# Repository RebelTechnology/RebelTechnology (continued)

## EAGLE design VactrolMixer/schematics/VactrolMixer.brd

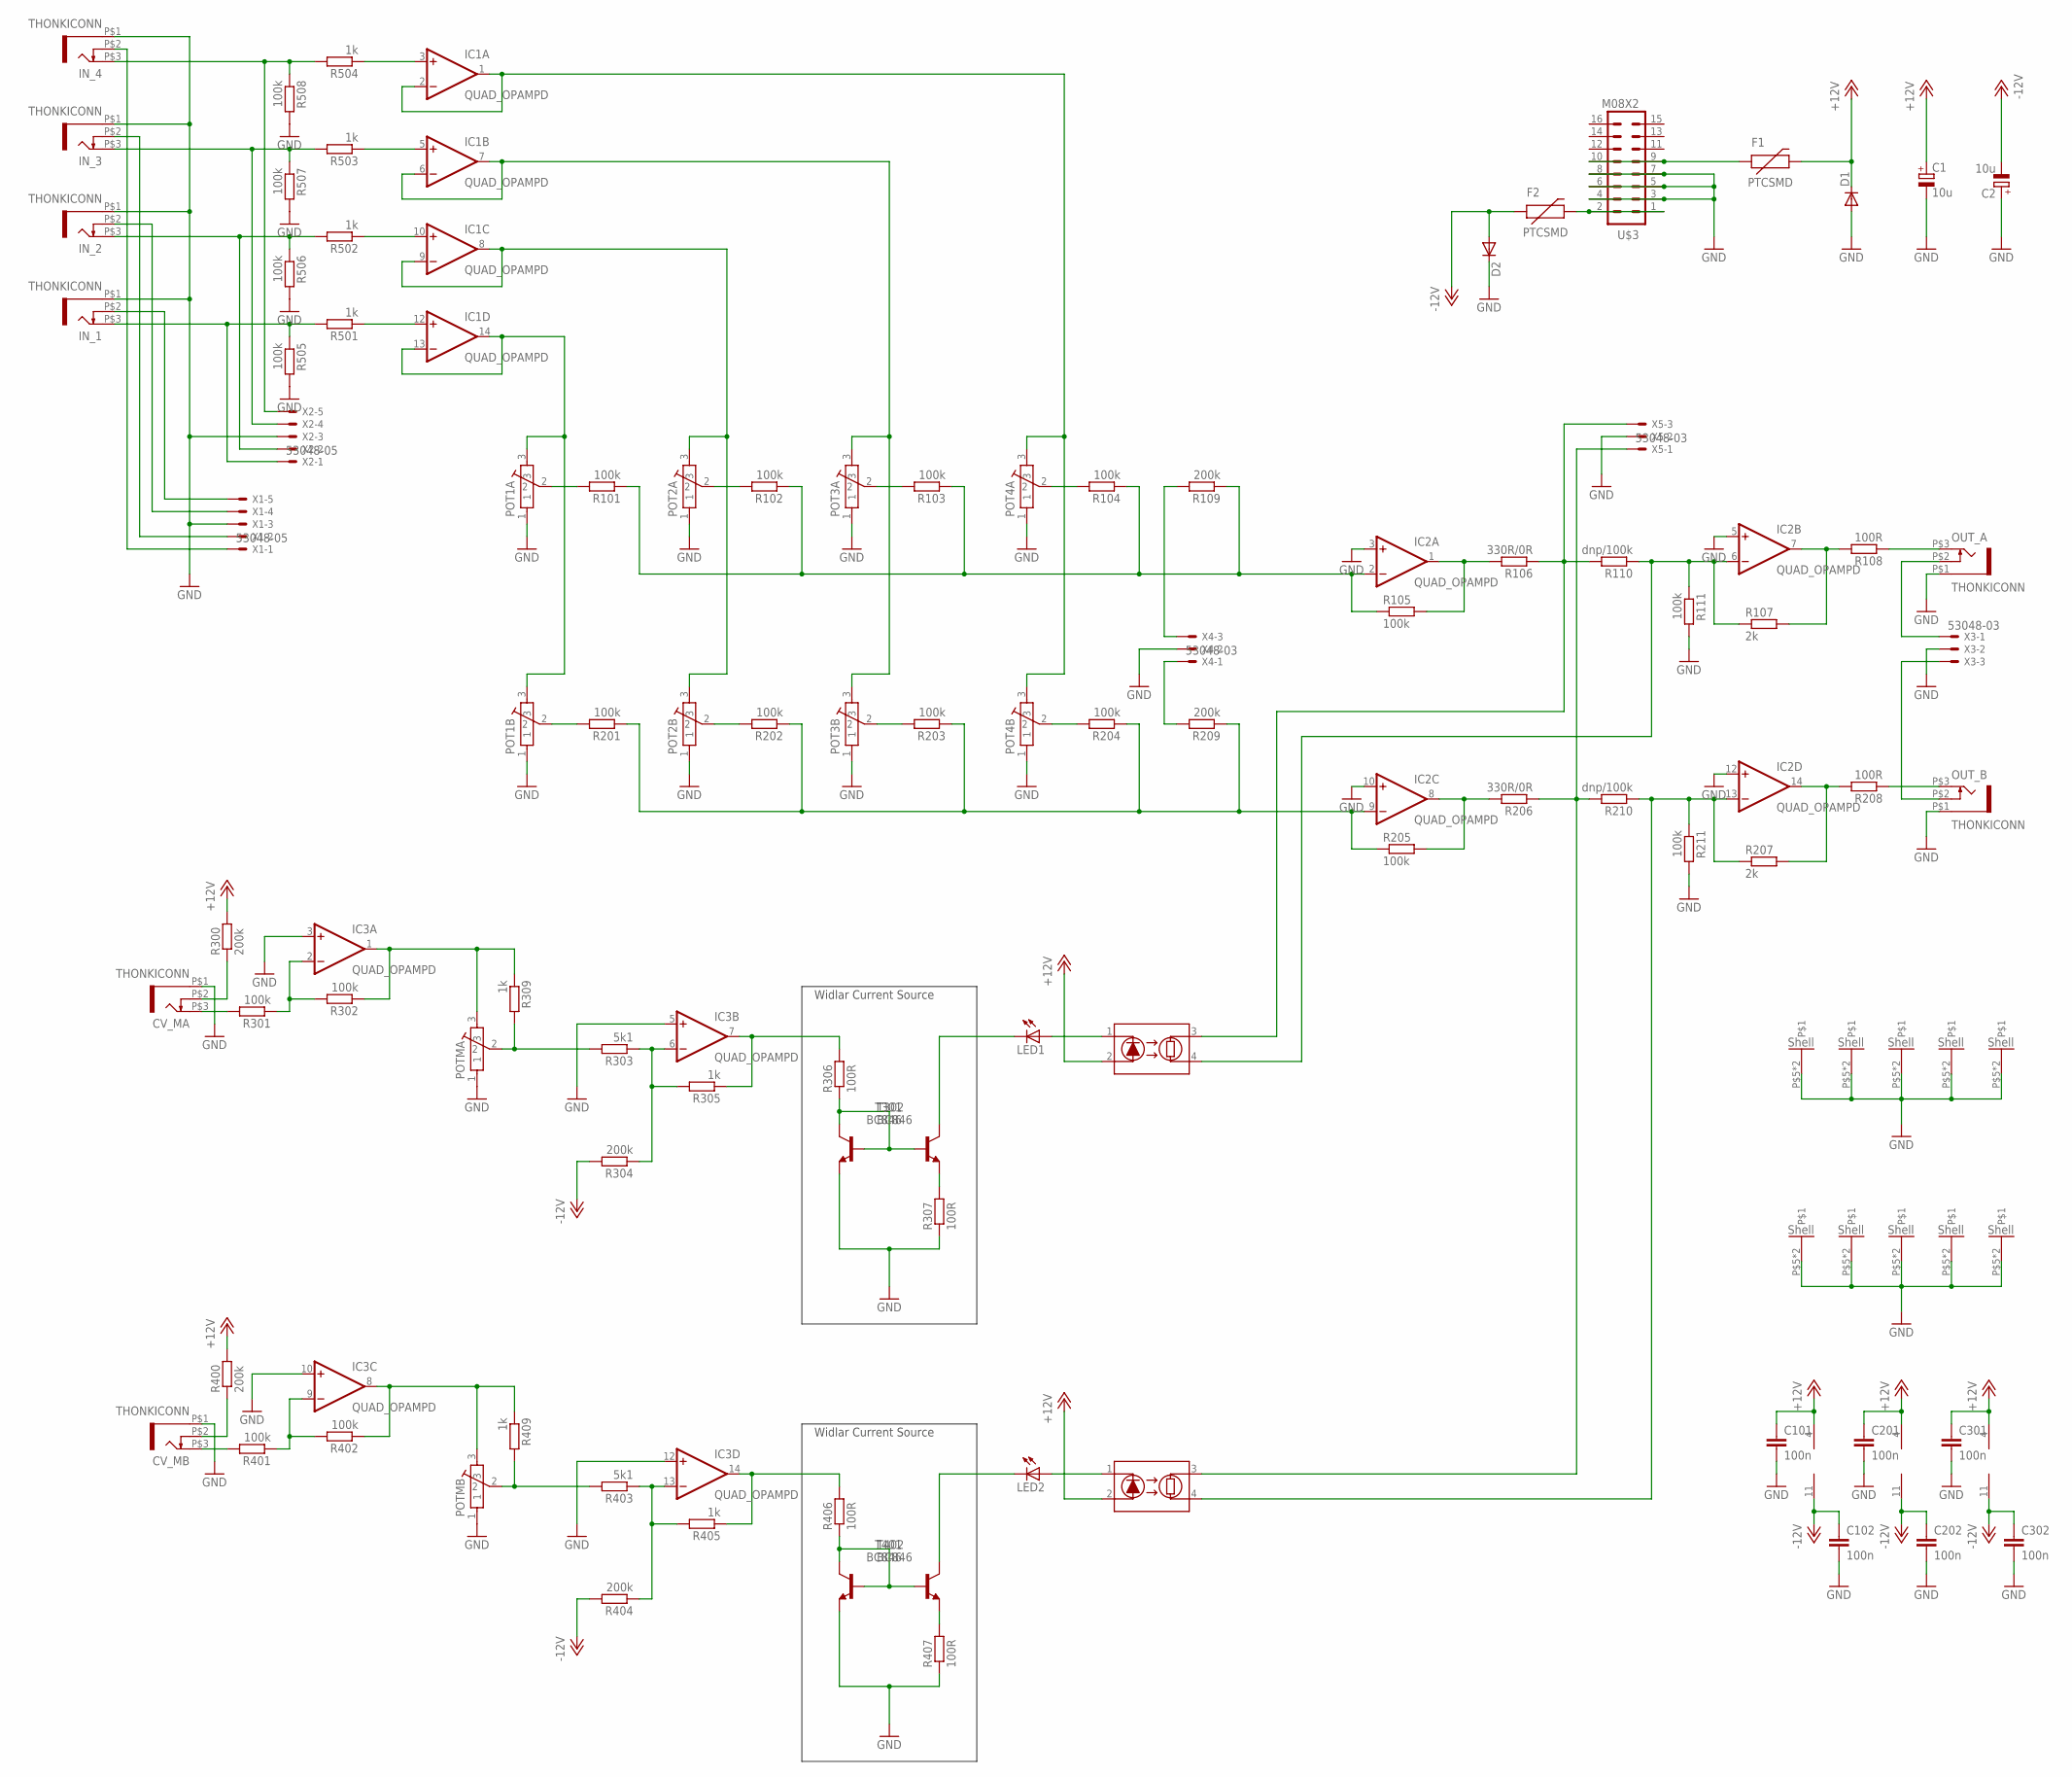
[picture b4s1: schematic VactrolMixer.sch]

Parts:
C1, C2: 10u; 153CLV-0605
C101, C102, C201, C202, C301, C302: 100n; C0603
CV_MA: THONKICONN
CV_MB: THONKICONN
D1, D2: DIODESMA; SMA-DIODE
F1, F2: PTCSMD; PTC-1206
IC1, IC2, IC3: QUAD_OPAMPD; SO14
IN_1, IN_2, IN_3, IN_4: THONKICONN
LED1, LED2: LED3MM
OUT_A: THONKICONN
OUT_B: THONKICONN
POT1A, POT1B, POT2A, POT2B, POT3A, POT3B, POT4A, POT4B: POT-ALPS-RK09L1140
POTMA: POT-ALPS-RK09L1140
POTMB: POT-ALPS-RK09L1140
R101, R102, R103, R104, R105, R111, R201, R202, R203, R204, R205, R211, R301, R302, R401, R402, R505, R506, R507, R508: 100k; R0603
R106, R206: 330R/0R; R0603
R107, R207: 2k; R0603
R108, R208, R306, R307, R406, R407: 100R; R0603
R109, R209, R300, R304, R400, R404: 200k; R0603
R110, R210: dnp/100k; R0603
R303, R403: 5k1; R0603
R305, R309, R405, R409, R501, R502, R503, R504: 1k; R0603
T301, T302, T401, T402: BC846; SOT23
U$3: M08X2; 2X8
VAC1, VAC2: VTL5C3
X1, X2: 53048-05
X3, X4, X5: 53048-03

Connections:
+12V: C1.+, C101.1, C201.1, C301.1, D1.C, F1.2, IC1.4 (V+), IC2.4 (V+), IC3.4 (V+), R300.2, R400.2, VAC1.2 (LED+), VAC2.2 (LED+)
-12V: C2.-, C102.1, C202.1, C302.1, D2.A, F2.1, IC1.11 (V-), IC2.11 (V-), IC3.11 (V-), R304.2, R404.2
CV_SW_A: CV_MA.P$2 (4), R300.1
CV_SW_B: CV_MB.P$2 (4), R400.1
GND: C1.-, C2.+, C101.2, C102.2, C201.2, C202.2, C301.2, C302.2, CV_MA.P$1 (5), CV_MB.P$1 (5), D1.A, D2.C, IC2.3 (+IN), IC2.5 (+IN), IC2.10 (+IN), IC2.12 (+IN), IC3.3 (+IN), IC3.5 (+IN), IC3.10 (+IN), IC3.12 (+IN), IN_1.P$1 (5), IN_2.P$1 (5), IN_3.P$1 (5), IN_4.P$1 (5), OUT_A.P$1 (5), OUT_B.P$1 (5), POT1A.1, POT1A.P$5, POT1A.P$6, POT1B.1, POT1B.P$5, POT1B.P$6, POT2A.1, POT2A.P$5, POT2A.P$6, POT2B.1, POT2B.P$5, POT2B.P$6, POT3A.1, POT3A.P$5, POT3A.P$6, POT3B.1, POT3B.P$5, POT3B.P$6, POT4A.1, POT4A.P$5, POT4A.P$6, POT4B.1, POT4B.P$5, POT4B.P$6, POTMA.1, POTMA.P$5, POTMA.P$6, POTMB.1, POTMB.P$5, POTMB.P$6, R111.2, R211.2, R307.1, R407.1, R505.2, R506.2, R507.2, R508.2, T301.2 (E), T401.2 (E), U$3.3, U$3.4, U$3.5, U$3.6, U$3.7, U$3.8, X1.3, X2.3, X3.2, X4.2, X5.2
INV_OUT_A: R106.1, R110.2, VAC1.3 (LDRA), X5.3
INV_OUT_B: R206.1, R210.2, VAC2.3 (LDRA), X5.1
IN_1: IN_1.P$3 (3), R501.2, R505.1, X2.1
IN_2: IN_2.P$3 (3), R502.2, R506.1, X2.2
IN_3: IN_3.P$3 (3), R503.2, R507.1, X2.4
IN_4: IN_4.P$3 (3), R504.2, R508.1, X2.5
IN_5_A: R109.2, X4.3
IN_5_B: R209.2, X4.1
unnamed: IC2.7 (OUT), R107.2, R108.2
unnamed: POT2B.2, R202.2
unnamed: IC1.3 (+IN), R504.1
unnamed: CV_MA.P$3 (3), R301.2
unnamed: IC2.1 (OUT), R105.2, R106.2
unnamed: IC2.8 (OUT), R205.2, R206.2
unnamed: POT3B.2, R203.2
unnamed: IC2.6 (-IN), R107.1, R110.1, R111.1, VAC1.4 (LDRB)
unnamed: POT1A.2, R101.2
unnamed: IC2.14 (OUT), R207.2, R208.2
unnamed: LED2.A, VAC2.1 (LED-)
unnamed: IC1.5 (+IN), R503.1
unnamed: POT4B.2, R204.2
unnamed: CV_MB.P$3 (3), R401.2
unnamed: IC1.8 (OUT), IC1.9 (-IN), POT2A.3, POT2B.3
unnamed: IC1.13 (-IN), IC1.14 (OUT), POT1A.3, POT1B.3
unnamed: POT4A.2, R104.2
unnamed: R407.2, T402.2 (E)
unnamed: R406.1, T401.1 (B), T401.3 (C), T402.1 (B)
unnamed: LED2.K (C), T402.3 (C)
unnamed: POT3A.2, R103.2
unnamed: POT1B.2, R201.2
unnamed: POT2A.2, R102.2
unnamed: R307.2, T302.2 (E)
unnamed: IC2.13 (-IN), R207.1, R210.1, R211.1, VAC2.4 (LDRB)
unnamed: LED1.A, VAC1.1 (LED-)
unnamed: LED1.K (C), T302.3 (C)
unnamed: IC3.7 (OUT), R305.1, R306.2
unnamed: R306.1, T301.1 (B), T301.3 (C), T302.1 (B)
unnamed: IC2.9 (-IN), R201.1, R202.1, R203.1, R204.1, R205.1, R209.1
unnamed: IC1.10 (+IN), R502.1
unnamed: IC1.12 (+IN), R501.1
unnamed: IC2.2 (-IN), R101.1, R102.1, R103.1, R104.1, R105.1, R109.1
unnamed: IC1.6 (-IN), IC1.7 (OUT), POT3A.3, POT3B.3
unnamed: F1.1, U$3.9, U$3.10
unnamed: F2.2, U$3.1, U$3.2
unnamed: IC1.1 (OUT), IC1.2 (-IN), POT4A.3, POT4B.3
unnamed: IC3.2 (-IN), R301.1, R302.2
unnamed: IC3.1 (OUT), POTMA.3, R302.1, R309.1
unnamed: IC3.6 (-IN), R303.1, R304.1, R305.2
unnamed: POTMA.2, R303.2, R309.2
unnamed: IC3.9 (-IN), R401.1, R402.2
unnamed: IC3.8 (OUT), POTMB.3, R402.1, R409.1
unnamed: IC3.14 (OUT), R405.1, R406.2
unnamed: IC3.13 (-IN), R403.1, R404.1, R405.2
unnamed: POTMB.2, R403.2, R409.2
OUT_A: OUT_A.P$3 (3), R108.1
OUT_B: OUT_B.P$3 (3), R208.1
SW_IN_1: IN_1.P$2 (4), X1.5
SW_IN_2: IN_2.P$2 (4), X1.4
SW_IN_3: IN_3.P$2 (4), X1.2
SW_IN_4: IN_4.P$2 (4), X1.1
SW_OUT_A: OUT_A.P$2 (4), X3.1
SW_OUT_B: OUT_B.P$2 (4), X3.3

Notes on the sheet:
Widlar Current Source

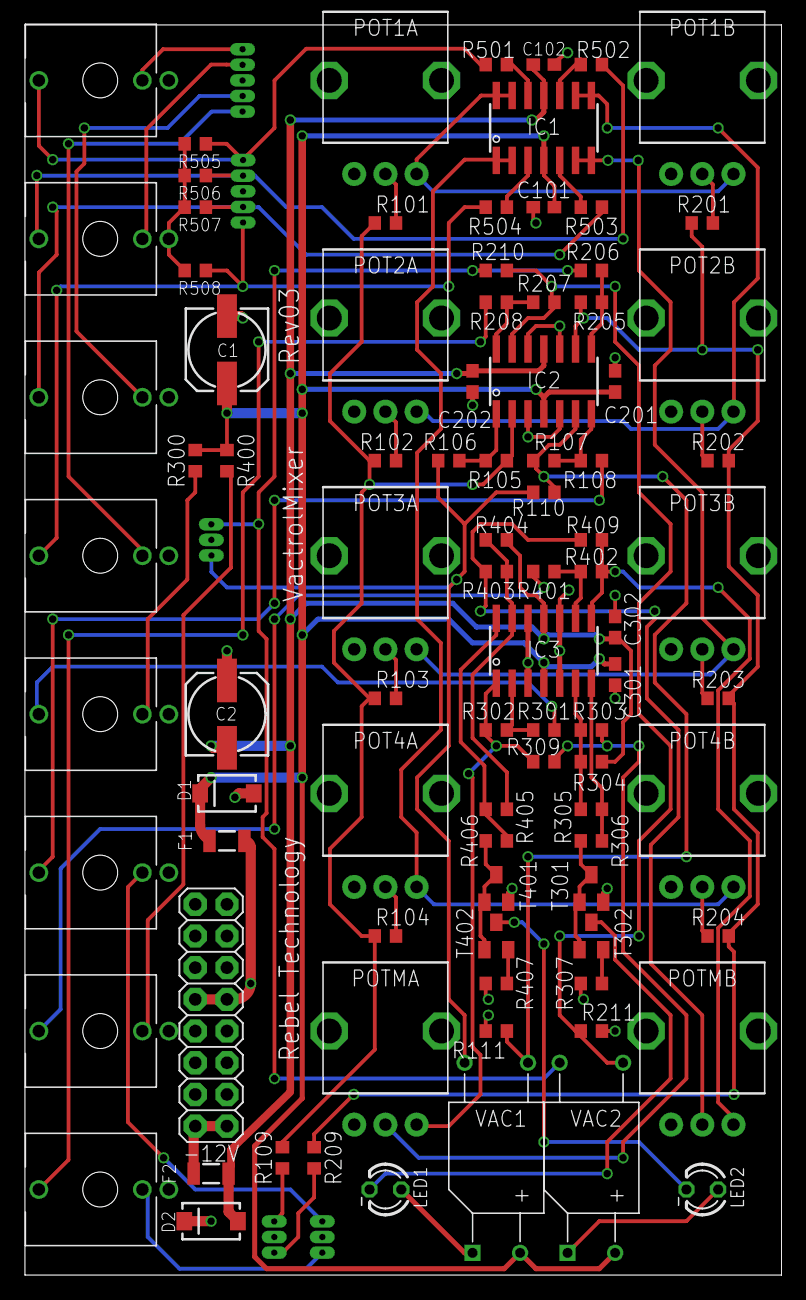
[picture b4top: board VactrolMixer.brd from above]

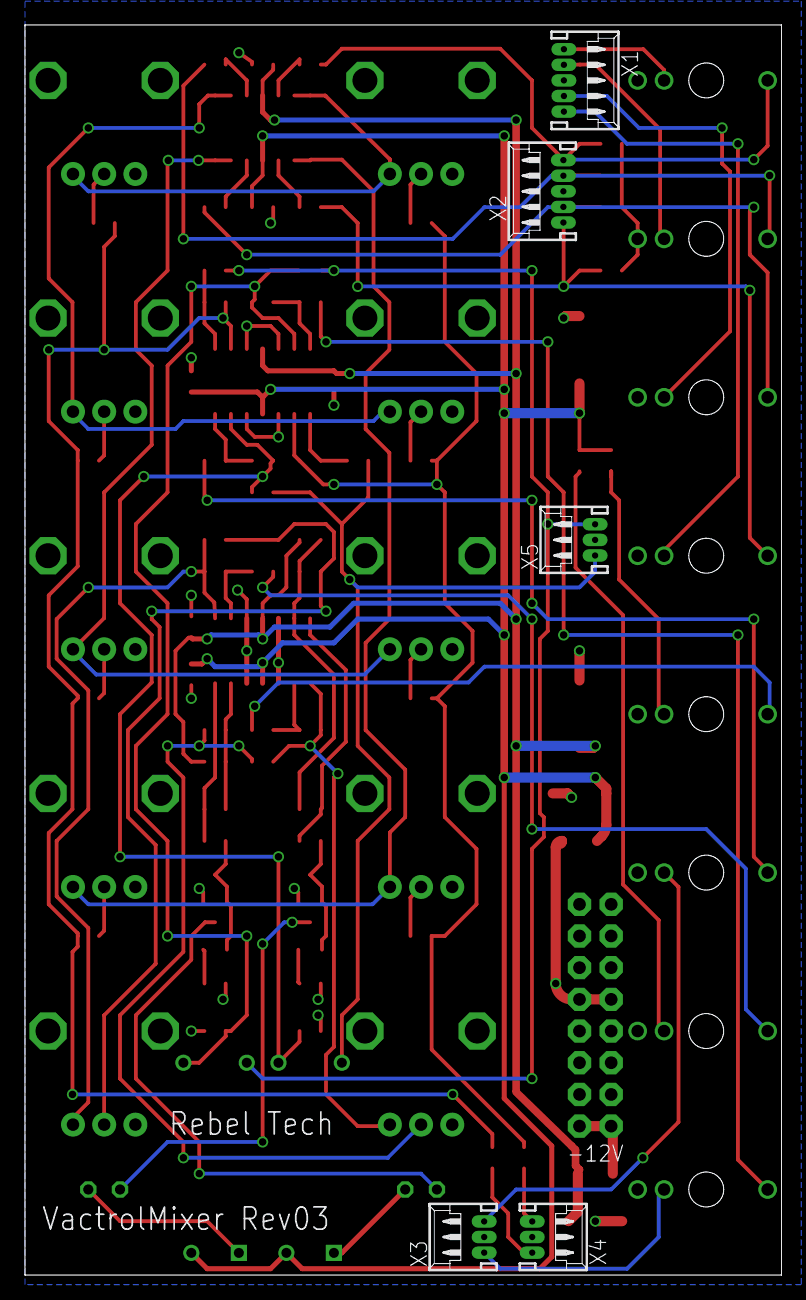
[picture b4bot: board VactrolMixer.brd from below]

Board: 2 copper layers, 60.6 x 100.2 mm, 95 parts (5 on the bottom side), 67 nets.

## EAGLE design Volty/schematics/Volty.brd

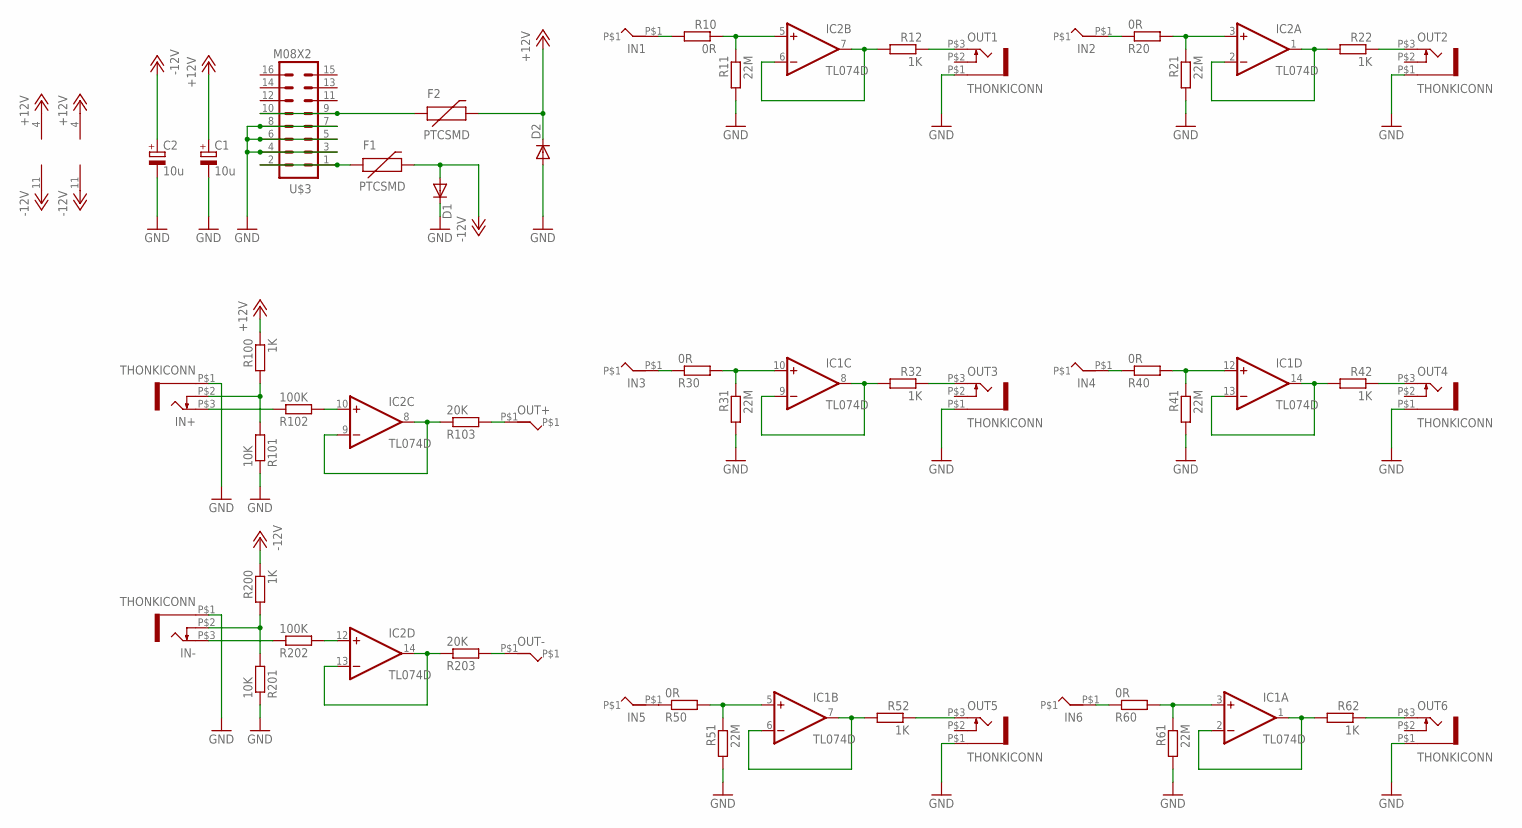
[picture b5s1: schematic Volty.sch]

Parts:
C1, C2: 10u; E2,5-6
D1, D2: DIODESMA; SMA-DIODE
F1, F2: PTCSMD; PTC-1206
IC1, IC2: TL074D; SO14
IN1, IN2, IN3, IN4, IN5, IN6: BANANAJACK
IN+: THONKICONN
IN-: THONKICONN
OUT1, OUT2, OUT3, OUT4, OUT5, OUT6: THONKICONN
OUT+: BANANAJACK
OUT-: BANANAJACK
R10, R20, R30, R40, R50, R60: 0R; 0603
R11, R21, R31, R41, R51, R61: 22M; 0603
R12, R22, R32, R42, R52, R62, R100, R200: 1K; 0603
R101, R201: 10K; 0603
R102, R202: 100K; 0603
R103, R203: 20K; 0603
U$3: M08X2; 2X8

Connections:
+12V: C1.+, D2.C, F2.2, IC1.4 (V+), IC2.4 (V+), R100.1
-12V: C2.+, D1.A, F1.2, IC1.11 (V-), IC2.11 (V-), R200.1
GND: C1.-, C2.-, D1.C, D2.A, IN+.P$1 (5), IN-.P$1 (5), OUT1.P$1 (5), OUT2.P$1 (5), OUT3.P$1 (5), OUT4.P$1 (5), OUT5.P$1 (5), OUT6.P$1 (5), R11.2, R21.2, R31.2, R41.2, R51.2, R61.2, R101.1, R201.1, U$3.3, U$3.4, U$3.5, U$3.6, U$3.7, U$3.8
unnamed: IN6.P$1, R60.1
unnamed: IN2.P$1, R20.1
unnamed: IC2.10 (+IN), R102.2
unnamed: IN+.P$2 (4), R100.2, R101.2
unnamed: F1.1, U$3.1, U$3.2
unnamed: F2.1, U$3.9, U$3.10
unnamed: IN1.P$1, R10.2
unnamed: IN3.P$1, R30.1
unnamed: IC2.6 (-IN), IC2.7 (OUT), R12.2
unnamed: OUT1.P$3 (3), R12.1
unnamed: IN5.P$1, R50.1
unnamed: IC2.5 (+IN), R10.1, R11.1
unnamed: IN+.P$3 (3), R102.1
unnamed: OUT+.P$1, R103.2
unnamed: IC2.8 (OUT), IC2.9 (-IN), R103.1
unnamed: OUT-.P$1, R203.2
unnamed: IC2.13 (-IN), IC2.14 (OUT), R203.1
unnamed: IN4.P$1, R40.1
unnamed: IC2.12 (+IN), R202.2
unnamed: IN-.P$3 (3), R202.1
unnamed: IN-.P$2 (4), R200.2, R201.2
unnamed: IC2.3 (+IN), R20.2, R21.1
unnamed: IC1.3 (+IN), R60.2, R61.1
unnamed: IC1.12 (+IN), R40.2, R41.1
unnamed: OUT3.P$3 (3), R32.1
unnamed: OUT5.P$3 (3), R52.1
unnamed: IC1.8 (OUT), IC1.9 (-IN), R32.2
unnamed: IC1.6 (-IN), IC1.7 (OUT), R52.2
unnamed: IC1.5 (+IN), R50.2, R51.1
unnamed: OUT4.P$3 (3), R42.1
unnamed: OUT6.P$3 (3), R62.1
unnamed: OUT2.P$3 (3), R22.1
unnamed: IC2.1 (OUT), IC2.2 (-IN), R22.2
unnamed: IC1.13 (-IN), IC1.14 (OUT), R42.2
unnamed: IC1.1 (OUT), IC1.2 (-IN), R62.2
unnamed: IC1.10 (+IN), R30.2, R31.1

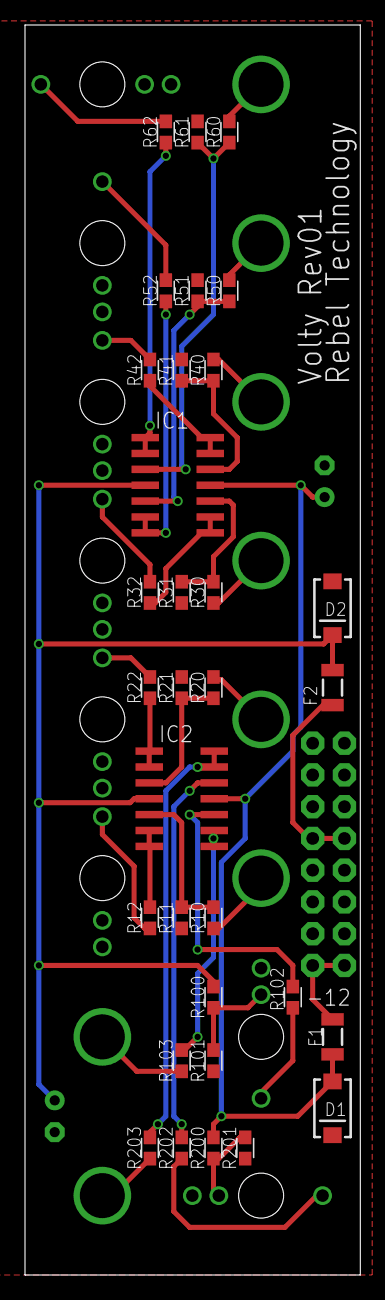
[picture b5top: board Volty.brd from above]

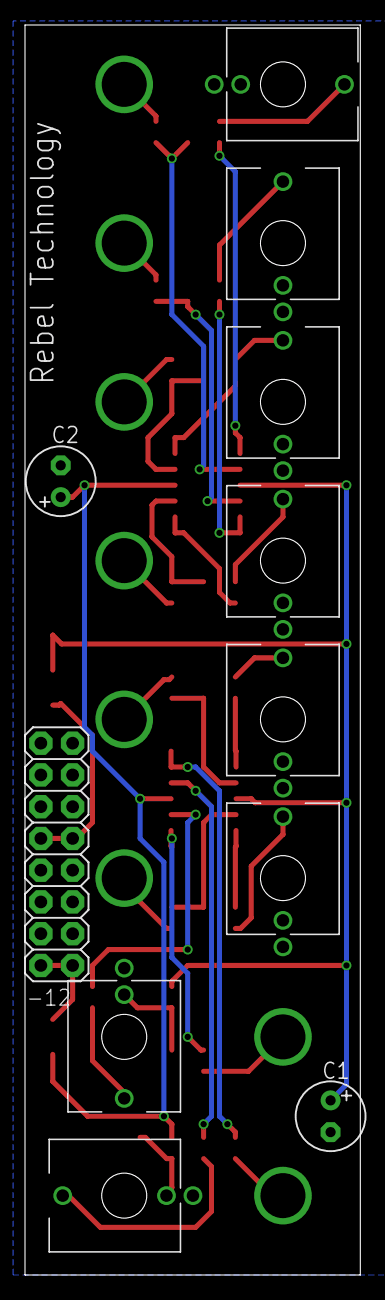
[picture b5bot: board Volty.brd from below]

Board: 2 copper layers, 26.8 x 100.0 mm, 51 parts (19 on the bottom side), 39 nets.

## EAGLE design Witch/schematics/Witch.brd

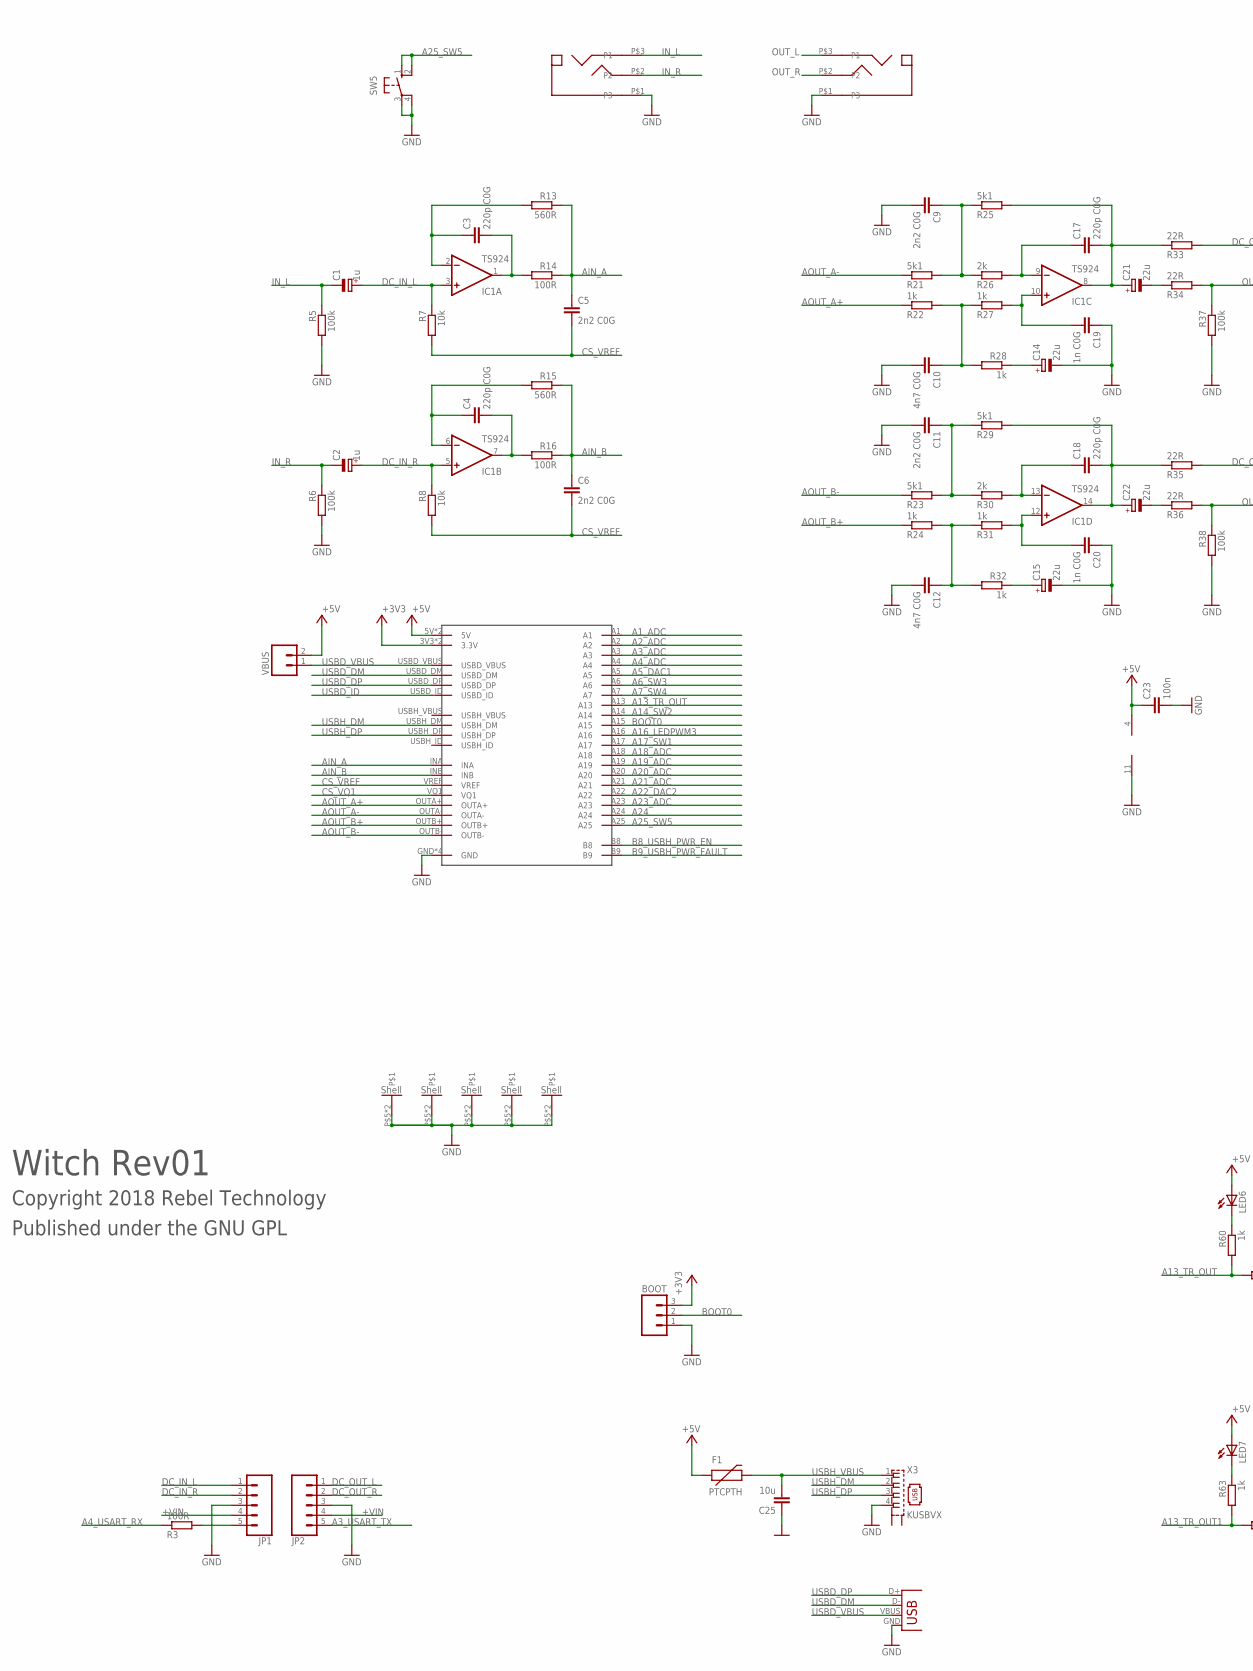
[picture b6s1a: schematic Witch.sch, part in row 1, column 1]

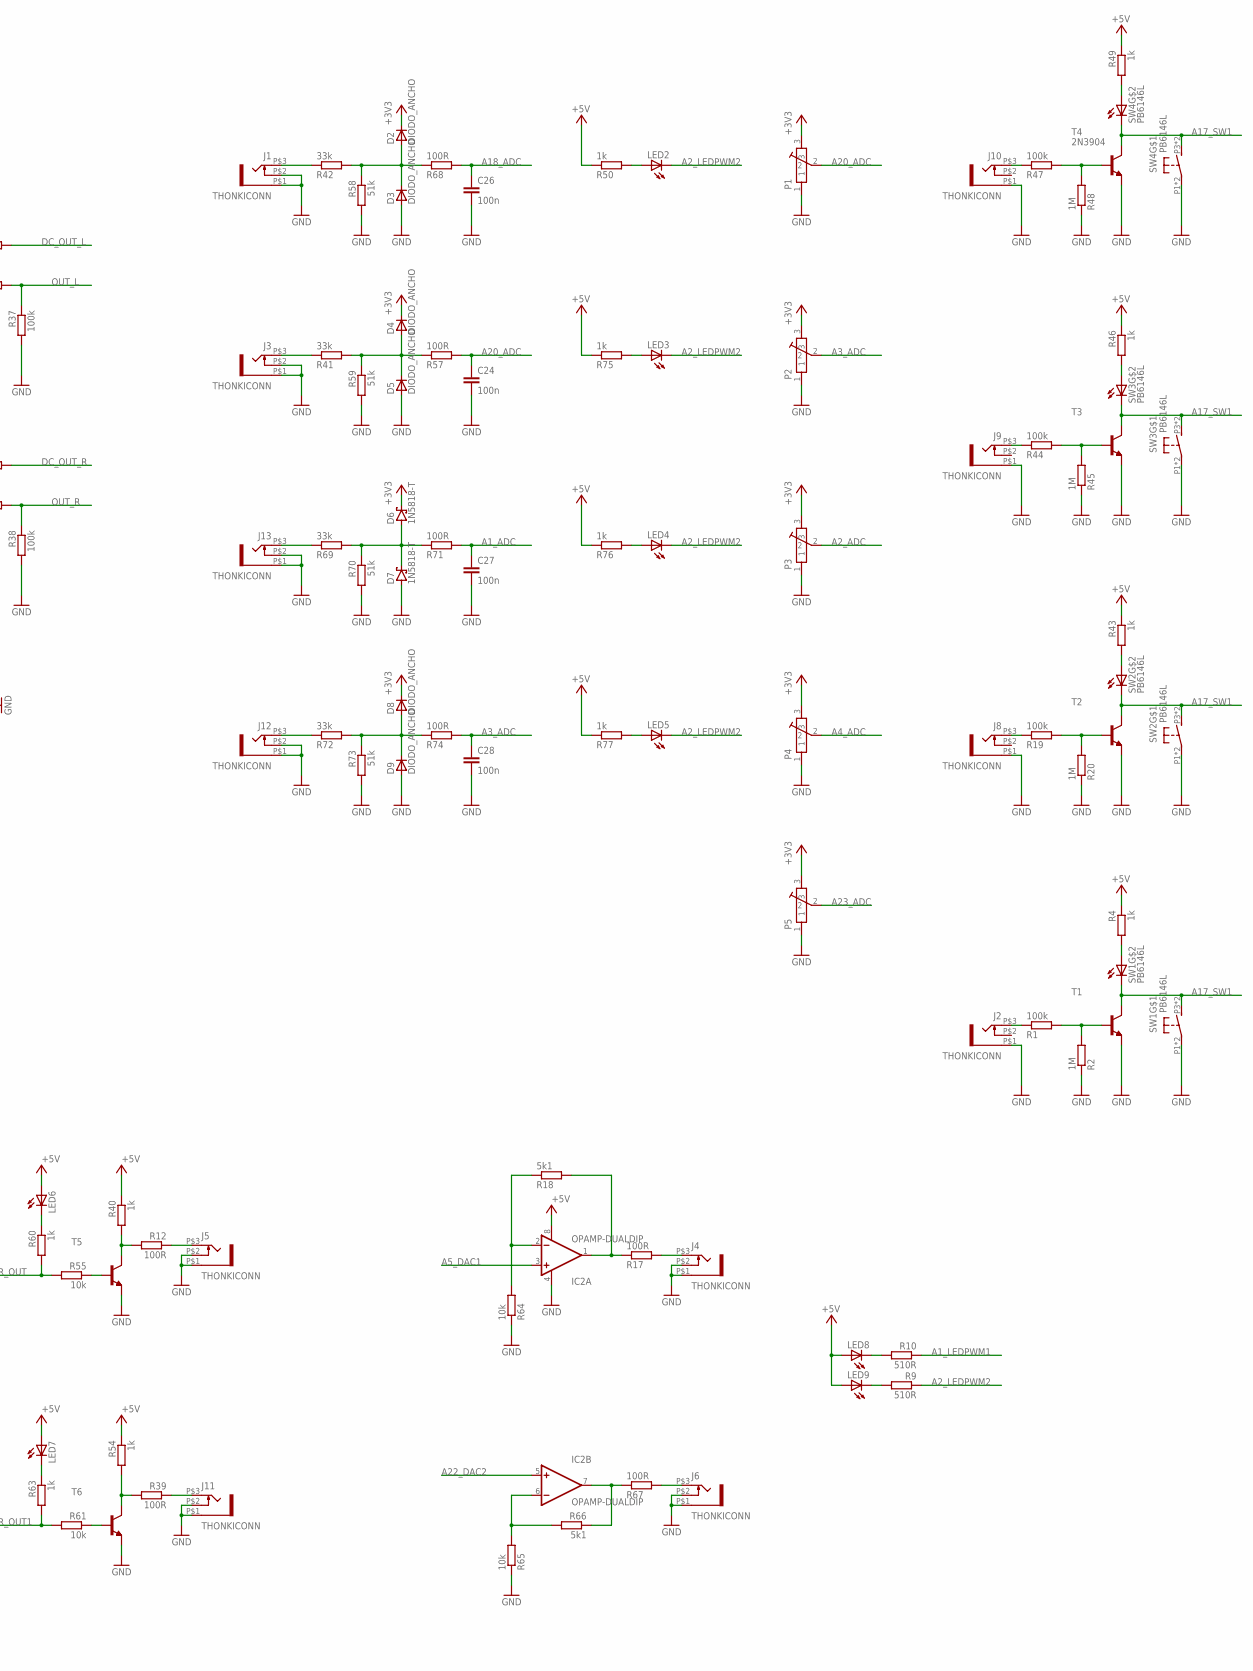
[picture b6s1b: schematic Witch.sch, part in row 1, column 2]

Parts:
BOOT: M03PTH; 1X03
C1, C2: 1u; E1,8-4
C3, C4, C17, C18: 220p C0G; C050-025X075
C5, C6, C9, C11: 2n2 C0G; C050-025X075
C10, C12: 4n7 C0G; C050-025X075
C14, C15, C21, C22: 22u; E1,8-4
C19, C20: 1n C0G; C050-025X075
C23, C24, C26, C27, C28: 100n; C050-025X075
C25: 10u; C050-025X075
D2, D3, D4, D5, D8, D9: DIODO_ANCHO; D-5.2
D6, D7: 1N5818-T; DO41-7.6
F1: PTCPTH; PTC
IC1: TS924; DIL14
IC2: OPAMP-DUALDIP; DIP08
J1, J2, J3, J4, J5, J6, J8, J9, J10, J11, J12, J13: THONKICONN
JP1, JP2: CONN_05JST-VERT; JST-5-PTH-VERT
LED2, LED3, LED4, LED5, LED6, LED7, LED8, LED9: LED3MM
P1, P2, P3, P4, P5: POT-ALPS-RK09L1140
R1, R5, R6, R19, R37, R38, R44, R47: 100k; 0204/5
R2, R45, R48: 1M; 0204/5
R3, R12, R14, R16, R17, R39, R57, R67, R68, R71, R74: 100R; 0204/5
R4, R22, R24, R27, R28, R31, R32, R40, R43, R46, R49, R50, R54, R60, R63, R75, R76, R77: 1k; 0204/5
R7, R8, R55, R61, R64, R65: 10k; 0204/5
R9, R10: 510R; 0204/5
R13, R15: 560R; 0204/5
R18, R21, R23, R25, R29, R66: 5k1; 0204/5
R20: 1M; 0204/7
R26, R30: 2k; 0204/5
R33, R34, R35, R36: 22R; 0204/5
R41, R42, R69, R72: 33k; 0204/5
R58, R59, R70, R73: 51k; 0204/5
SW1, SW2, SW3, SW4: PB6146L
SW5: 10-XX; B3F-10XX
T1, T2, T3, T5, T6: 2N3904-NPN-TO92-EBC; TO92-EBC
T4: 2N3904; TO92
U$4, U$5: THONKICONN_STEREO
U$10: OWL_DIGITAL_LITE_2USB
VBUS: M02PTH; 1X02
X3: KUSBVX
X5: USBPTH-VERTICAL; USB-B-PTH-VERTICAL

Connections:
+3V3: BOOT.3, D2.C, D4.C, D6.C, D8.C, P1.3, P2.3, P3.3, P4.3, P5.3, U$10.3V3 (3.3V), U$10.3V3_2 (3.3V)
+5V: C23.1, F1.P$1 (1), IC1.4 (V+), IC2.8 (V+), LED6.A, LED7.A, LED8.A, LED9.A, R4.1, R40.1, R43.1, R46.1, R49.1, R50.1, R54.1, R75.1, R76.1, R77.1, U$10.5V, U$10.5V_2 (5V), VBUS.2
+VIN: JP1.4, JP2.4
A1_ADC: C27.1, R71.2, U$10.A1
A1_LEDPWM1: R10.1
A2_ADC: P3.2, U$10.A2
A2_LEDPWM2: LED2.K (C), LED3.K (C), LED4.K (C), LED5.K (C), R9.1
A3_ADC: C28.1, R74.2, U$10.A3
A3_USART_TX: JP2.5
A4_ADC: P4.2, U$10.A4
A4_USART_RX: R3.1
A5_DAC1: IC2.3 (+IN), U$10.A5
A6_SW3: U$10.A6
A7_SW4: U$10.A7
A13_TR_OUT: R55.2, R60.2, U$10.A13
A13_TR_OUT1: R61.2, R63.2
A14_SW2: U$10.A14
A16_LEDPWM3: U$10.A16
A17_SW1: SW1.P3 (S), SW1.P4 (S), SW1.PL2 (C), SW2.P3 (S), SW2.P4 (S), SW2.PL2 (C), SW3.P3 (S), SW3.P4 (S), SW3.PL2 (C), SW4.P3 (S), SW4.P4 (S), SW4.PL2 (C), T1.C, T2.C, T3.C, T4.1 (C), U$10.A17
A18_ADC: C26.1, R68.2, U$10.A18
A19_ADC: P1.2, U$10.A19
A20_ADC: C24.1, R57.2, U$10.A20
A21_ADC: P2.2, U$10.A21
A22_DAC2: IC2.5 (+IN), U$10.A22
A23_ADC: P5.2, U$10.A23
A24: U$10.A24
A25_SW5: SW5.1 (S), SW5.2 (S1), U$10.A25
AIN_A: C5.1, R13.1, R14.1, U$10.INA
AIN_B: C6.1, R15.1, R16.1, U$10.INB
AOUT_A+: R22.1, U$10.OUTA+
AOUT_A-: R21.1, U$10.OUTA-
AOUT_B+: R24.1, U$10.OUTB+
AOUT_B-: R23.1, U$10.OUTB-
B8_USBH_PWR_EN: U$10.B8
B9_USBH_PWR_FAULT: U$10.B9
BOOT0: BOOT.2, U$10.A15
CS_VQ1: U$10.VQ1
CS_VREF: C5.2, C6.2, R7.2, R8.2, U$10.VREF
DC_IN_L: C1.+, IC1.3 (+IN), JP1.1, R7.1
DC_IN_R: C2.+, IC1.5 (+IN), JP1.2, R8.1
DC_OUT_L: JP2.1, R33.2
DC_OUT_R: JP2.2, R35.2
GND: BOOT.1, C9.2, C10.2, C11.2, C12.2, C14.-, C15.-, C19.1, C20.1, C23.2, C24.2, C25.1, C26.2, C27.2, C28.2, D3.A, D5.A, D7.A, D9.A, IC1.11 (V-), IC2.4 (V-), J1.P$1 (5), J1.P$2 (4), J2.P$1 (5), J3.P$1 (5), J3.P$2 (4), J4.P$1 (5), J4.P$2 (4), J5.P$1 (5), J5.P$2 (4), J6.P$1 (5), J6.P$2 (4), J8.P$1 (5), J9.P$1 (5), J10.P$1 (5), J11.P$1 (5), J11.P$2 (4), J12.P$1 (5), J12.P$2 (4), J13.P$1 (5), J13.P$2 (4), JP1.3, JP2.3, P1.1, P1.P$5, P1.P$6, P2.1, P2.P$5, P2.P$6, P3.1, P3.P$5, P3.P$6, P4.1, P4.P$5, P4.P$6, P5.1, P5.P$5, P5.P$6, R2.1, R5.2, R6.2, R20.1, R37.2, R38.2, R45.1, R48.1, R58.2, R59.2, R64.1, R65.1, R70.2, R73.2, SW1.P1, SW1.P2, SW2.P1, SW2.P2, SW3.P1, SW3.P2, SW4.P1, SW4.P2, SW5.3, SW5.4 (P1), T1.E, T2.E, T3.E, T4.3 (E), T5.E, T6.E, U$4.P$1 (P3), U$5.P$1 (P3), U$10.GND, U$10.GND_2 (GND), U$10.GND_3 (GND), U$10.GND_4 (GND), X3.4, X5.GND
IN_L: C1.-, R5.1, U$4.P$3 (P1)
IN_R: C2.-, R6.1, U$4.P$2 (P2)
unnamed: JP1.5, R3.2
unnamed: J11.P$3 (3), R39.1
unnamed: C3.1, IC1.2 (-IN), R13.2
unnamed: C4.2, IC1.7 (OUT), R16.2
unnamed: C4.1, IC1.6 (-IN), R15.2
unnamed: C3.2, IC1.1 (OUT), R14.2
unnamed: C17.1, IC1.9 (-IN), R26.2
unnamed: C15.+, R32.1
unnamed: C21.-, R34.1
unnamed: C14.+, R28.1
unnamed: C19.2, IC1.10 (+IN), R27.2
unnamed: C18.2, C22.+, IC1.14 (OUT), R29.2, R35.1
unnamed: C22.-, R36.1
unnamed: LED8.K (C), R10.2
unnamed: C10.1, R22.2, R27.1, R28.2
unnamed: LED9.K (C), R9.2
unnamed: D4.A, D5.C, R41.2, R57.1, R59.1
unnamed: LED7.K (C), R63.1
unnamed: J5.P$3 (3), R12.1
unnamed: IC2.2 (-IN), R18.1, R64.2
unnamed: IC2.1 (OUT), R17.1, R18.2
unnamed: J2.P$3 (3), R1.1
unnamed: R39.2, R54.2, T6.C
unnamed: C11.1, R23.2, R29.1, R30.1
unnamed: R12.2, R40.2, T5.C
unnamed: C18.1, IC1.13 (-IN), R30.2
unnamed: J3.P$3 (3), R41.1
unnamed: R4.2, SW1.PL1 (A)
unnamed: R19.2, R20.2, T2.B
unnamed: C20.2, IC1.12 (+IN), R31.2
unnamed: R55.1, T5.B
unnamed: C12.1, R24.2, R31.1, R32.2
unnamed: J1.P$3 (3), R42.1
unnamed: J8.P$3 (3), R19.1
unnamed: R43.2, SW2.PL1 (A)
unnamed: R44.2, R45.2, T3.B
unnamed: R1.2, R2.2, T1.B
unnamed: J9.P$3 (3), R44.1
unnamed: C17.2, C21.+, IC1.8 (OUT), R25.2, R33.1
unnamed: R46.2, SW3.PL1 (A)
unnamed: C9.1, R21.2, R25.1, R26.1
unnamed: R47.2, R48.2, T4.2 (B)
unnamed: J10.P$3 (3), R47.1
unnamed: R49.2, SW4.PL1 (A)
unnamed: LED2.A, R50.2
unnamed: LED6.K (C), R60.1
unnamed: D2.A, D3.C, R42.2, R58.1, R68.1
unnamed: J13.P$3 (3), R69.1
unnamed: R61.1, T6.B
unnamed: D6.A, D7.C, R69.2, R70.1, R71.1
unnamed: J12.P$3 (3), R72.1
unnamed: J4.P$3 (3), R17.2
unnamed: IC2.6 (-IN), R65.2, R66.2
unnamed: IC2.7 (OUT), R66.1, R67.1
unnamed: J6.P$3 (3), R67.2
unnamed: D8.A, D9.C, R72.2, R73.1, R74.1
unnamed: LED3.A, R75.2
unnamed: LED4.A, R76.2
unnamed: LED5.A, R77.2
OUT_L: R34.2, R37.1, U$5.P$3 (P1)
OUT_R: R36.2, R38.1, U$5.P$2 (P2)
USBD_DM: U$10.USBD_DM, X5.D-
USBD_DP: U$10.USBD_DP, X5.D+
USBD_ID: U$10.USBD_ID
USBD_VBUS: U$10.USBD_VBUS, VBUS.1, X5.VBUS
USBH_DM: U$10.USBH_DM, X3.2
USBH_DP: U$10.USBH_DP, X3.3
USBH_VBUS: C25.2, F1.P$2 (2), X3.1

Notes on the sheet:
Witch Rev01
Copyright 2018 Rebel Technology
Published under the GNU GPL

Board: 2 copper layers, 157 parts (2 on the bottom side), 101 nets, no tracks yet.

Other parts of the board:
U$1, U$2: 2,8
U$6, U$7, U$8, U$9: 3,6
